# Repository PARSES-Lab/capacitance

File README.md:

# FDC1004 Capacitance Reading and Breakout Board Hardware 

This library provides basic functionality for the FDC1004 Capacitance to Digital Sensor. According to the datasheet, the FDC1004 provides femto-farad precision for measuring capacitances up to 115 pF in increments of 500 aF. The .ino files in examples demonstrate reading continuous values, triggered single values for multiple channels, and differential measurements. 

The breakout board provides shielded capacitance readings on four channels via a JST PH connector (v4). The board schematic and PCB files are included in the BreakoutBoard directory in this repository. Please see the Hardware file for more information about the breakout board design.

If you use this board in an academic project, please cite our work!

I. A. Mensah, D. Leblebicioglu and K. L. Dorsey, "Wireless Capacitive Measurement Board for Wearable or Proprioceptive Applications," 2025 IEEE 8th International Conference on Soft Robotics (RoboSoft), Lausanne, Switzerland, 2025, pp. 1-6, doi: 10.1109/RoboSoft63089.2025.11020828.

D. Leblebicioglu, I. A. Mensah, J. Allen, A. Vadivel, N. Hanson and K. L. Dorsey, "Capacitive Sensor Design for Soft Robots and Smart Garments," 2025 23rd International Conference on Solid-State Sensors, Actuators and Microsystems (Transducers), Orlando, FL, USA, 2025, pp. 414-418, doi: 10.1109/Transducers61432.2025.11110662.

## Hardware

 * A 3.3 V microcontroller board. The FDC1004 is incompatible with 5 V microcontrollers without additional care for the I2C bus voltage!
 * TI FDC1004: https://www.ti.com/product/FDC1004
 * 2 1.8k Ohm resistors to pull up SDA and SCL pins on I2C line (some microcontroller breakout boards may already have these on board)
 * A few non-polarized (e.g., ceramic) capacitors for test, in the range of 5 pF to 100 pF
 
## Limitations
 * This code has only been tested on the ESP32, ESP32-S2, and ESP32-S3 microcontroller breakout boards from Adafruit. It may not work on other 3.3 V microcontrollers such as the Adafruit Nano or Sparkfun Redboards that have 3.3 V logic levels. 
 * There is a potential bug when the FDC1004 is reading single (not repeated) measurements where it will read incorrectly. If you are getting unexpected behavior from the single read example, or no reading, push the continuous example first and then the single read example.

## Single-ended capacitance (channel to ground) or differential (channel to channel) readings: 
 * If first pin and second pin in configureMeasurement and triggerMeasurement functions are the same, it assumes a sigle-ended measurement
 * Otherwise, it assumes a differential measurement between those pins.
 * The convenience functions in the .cpp file (written by Beshaya) set the measurement type (single or continuous, which channels, measurement number/register)
 * Capacitors must always be placed from channel to ground. In differential measurements, they are still read by the difference between capacitance channels to ground. 

 ## Documentation on example functions
 
### float absoluteCapacitance(uint8_t measSlot, uint8_t chanA, uint8_t chanB, uint8_t measType, uint8_t * capdacPtr)
 * Calculates the absolute capaciance capacitanceAbsolute (relative + capdac) read off the FDC1004

 #### Parameters: 
 * measSlot : the measurement "slot" or number. This can be arbitrary between 0 and 3, or measA, measB... for convenience
 * chanA : the first pin you wish to measure capacitance to ground. Use pin definitions above for convenience.
 * chanB : the second pin you wish to measure capacitance to ground. Due to limitations of the FDC1004, chanB must be the same or greater value to chanA. Setting to the same value as chanA will set up a single-ended measurement. Setting at a higher value will set up a differential measurement. 
 * measType : Single (0) or repeated (1). Use measSingl and measCont for convenience. 
 * capdacPtr : A pointer to the global capdac value for that measurement. Labeled capdacA, capdacB... for convenience

 #### returns capacitanceAbsolute

* Notes: Calls configTrigRead in the case of a single measurement. Calls relativeCapacitance value in the case of a repeated measurement. If the returned capacitanceRelative reading is out of the +/- 15 pF limits for the FDC1004, it will call setCAPDAC. It converts capdac to a capacitance value in pF and adds to relative capacitance to find capacitanceAbsolute. If setCAPDAC was called, it will set the value of to capacitanceAbsolute -1

### float relativeCapacitance(uint8_t measSlot)
  * Reads the relative capacitance capacitanceRelative

#### Parameters: 
  * measSlot : the measurement "slot" or number. This can be arbitrary between 0 and 3, or measA, measB... for convenience

#### returns capacitanceRelative

* Notes: calls fdc.readMeasurement to read a 32-bit value (24-bit capacitance with 8 trailing zeroes, as per FDC1004 documentation) and convert into a capacitance reading with the ratio 15 pF/ 32676. The 16 most significant bits (MSB) are the only ones needed for the capacitance reading, since the measurement resolution is 0.5 fF and the max range is 30 pF. A 16 bit value in two's complement ranges from -32768 to 32767 (2^15 - 1) (i.e., resolution of ~0.46 fF with +/- 15 pF range). Therefore, we don't need to calculate the capacitance using the LSB since the most significant bit of LSB is below the measurement resolution/noise floor. We do still need to read LSB since the FDC1004 is expecting it to be read before the next measurement. The convenience functions in the .cpp file take care of this read.

### uint8_t setCAPDAC(uint8_t measSlot, uint8_t chanA, uint8_t chanB, uint8_t measType, uint8_t * capdacPtr)
* Resets capdac value. Will only execute if the measurement is single-ended (chanA and chanB are the same), because capdac cannot be set for a differential measurement.

#### Parameters:  
* measSlot : the measurement "slot" or number. This can be arbitrary between 0 and 3, or measA, measB... for convenience
* chanA : the first pin you wish to measure capacitance to ground. Use pin definitions above for convenience.
* chanB : the second pin you wish to measure capacitance to ground. Due to limitations of the FDC1004, chanB must be the same or greater value to chanA. Setting to the same value as chanA will set up a single-ended measurement. Setting at a higher value will set up a differential measurement. 
* measType : Single (0) or repeated (1). Use measSingl and measCont for convenience. 
* capdacPtr : the pointer to the global capdac associated with the measurement in measSlot

#### returns *capdacPtr (the dereference to the pointer to the global capdac associated with that measurement)

* Notes: Resets capdac to 0 and calls configTrigRead to read the relative value. While the new capdac value has not been found, it calls adjustCAPDAC, then calls configTrigRead in a loop until the timeout value (set to 30 by default). If a new capdac value is not found, it defaults to 0.

### uint8_t adjustCAPDAC(float capacitanceRelative, uint8_t * capdacPtr)
* Adjusts or increments capdac value and returns a flag stating whether it successfully reset.
 
#### Parameters: 
* capacitanceRelative : the relative capacitance reading fom the FDC
* capdacPtr : the pointer to the global capdac associated with the measurement in measSlot

#### returns capdacFlag, which says whether or not the capdac has been successfully reset.

* Notes: If the capdac is in range, it will try to find the capdac value that brings capacitanceRelative as close to 0 as possible to give the largest potential range, then return 0 to signal that capdac has been reset successfully. If capdac is not in range, it will incremenet or decrement capdac by 5 (15.625 pF) to bring it to the next range, then return 1 to signal that capdac needs to be set again.

### float configTrigRead(uint8_t measSlot, uint8_t chanA, uint8_t chanB, uint8_t measType, uint8_t capdac)
 * Configures and triggers the measurement and reads relative capacitance

 #### Parameters: 
 * measSlot : the measurement "slot" or number. This can be arbitrary between 0 and 3, or measA, measB... for convenience
 * chanA : the first pin you wish to measure capacitance to ground. Use pin definitions above for convenience.
 * chanB : the second pin you wish to measure capacitance to ground. Due to limitations of the FDC1004, chanB must be the same or greater value to chanA. Setting to the same value as chanA will set up a single-ended measurement. Setting at a higher value will set up a differential measurement. 
 * measType : Single (0) or repeated (1). Use measSingl and measCont for convenience. 
 * capdac : the global capdac value associated with that measurement.

 #### returns capacitanceRelative

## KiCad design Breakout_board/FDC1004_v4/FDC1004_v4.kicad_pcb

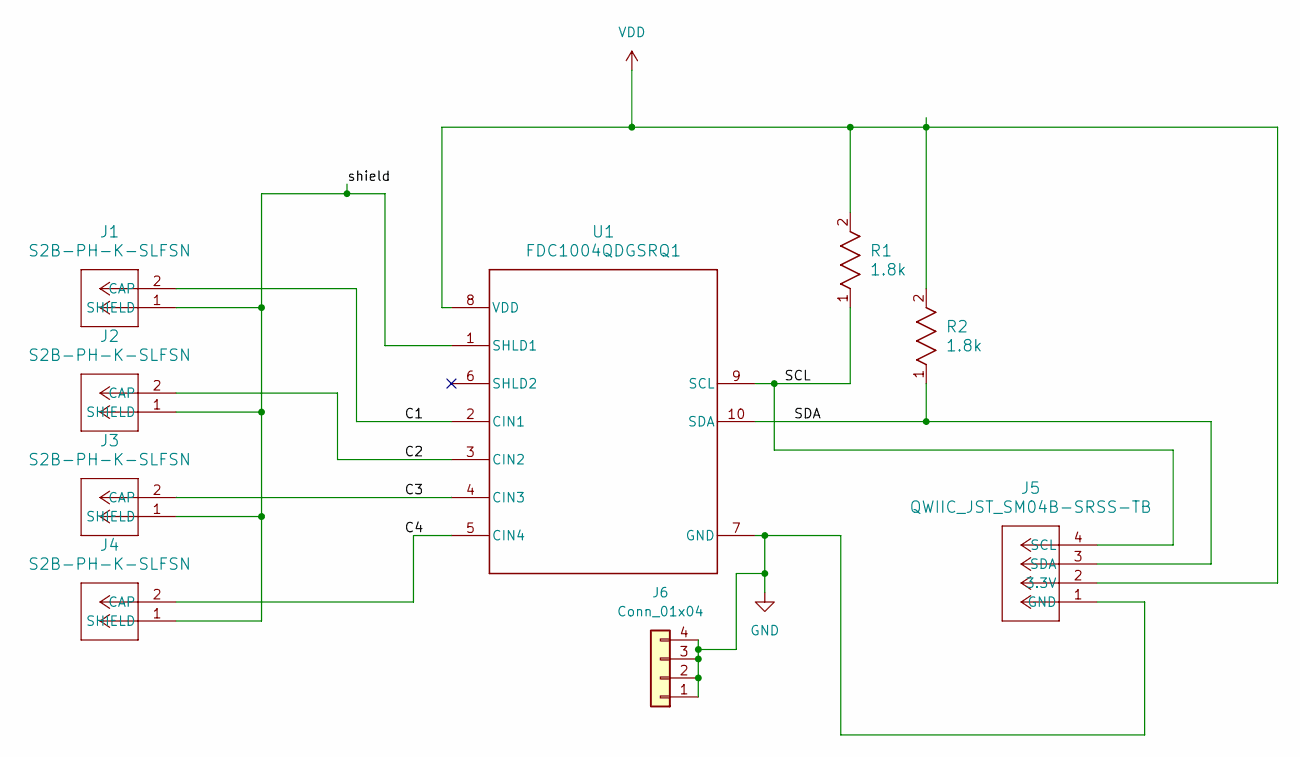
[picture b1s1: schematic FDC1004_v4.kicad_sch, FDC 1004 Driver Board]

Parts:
J1, J2, J3, J4: S2B-PH-K-SLFSN; CONN_S2B-PH-K-S_JST
J5: QWIIC_JST_SM04B-SRSS-TB; CONN_SM04B-SRSS-TB_JST_QWIIC
J6: Conn_01x04; PinHeader_1x04_P2.54mm_Vertical
R1, R2: 1.8k; R_1206_3216Metric_Pad1.30x1.75mm_HandSolder
U1: FDC1004QDGSRQ1; FDC1004DGS0010A_M

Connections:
/C1: J1.2 (CAP), U1.2 (CIN1)
/C2: J2.2 (CAP), U1.3 (CIN2)
/C3: J3.2 (CAP), U1.4 (CIN3)
/SCL: J5.4 (SCL), R1.1, U1.9 (SCL)
/SDA: J5.3 (SDA), R2.1, U1.10 (SDA)
/shield: J1.1 (SHIELD), J2.1 (SHIELD), J3.1 (SHIELD), J4.1 (SHIELD), U1.1 (SHLD1)
GND: J5.1 (GND), J6.1, J6.2, J6.3, J6.4, U1.7 (GND)
unnamed: J4.2 (CAP), U1.5 (CIN4)
VDD: J5.2 (3.3V), R1.2, R2.2, U1.8 (VDD)

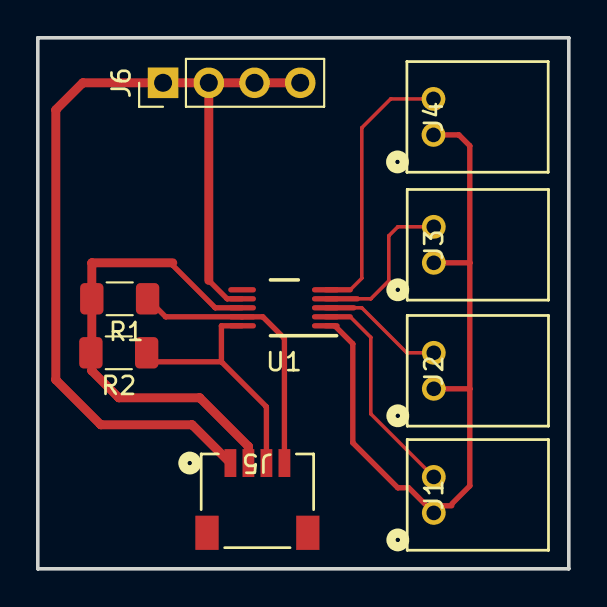
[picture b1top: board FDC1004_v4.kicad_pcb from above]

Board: 2 copper layers, 29.5 x 29.5 mm, 9 parts (0 on the bottom side), 9 nets.

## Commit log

2025-02-04 add missing semicolon
2025-03-10 update sampling rate in multichannel_read
2025-03-10 move functions to FDC1004 library
2025-04-09 Added capacitance arduino code and steps for logging capacitance and optitrack data
2025-04-14 serial communication ros2 topic echo is updated
2025-04-14 this is the serial communication code.
2025-04-14 Update steps for immanuel
2025-07-17 Update and rename miniFrank.py to ros_cap_publisher.py
    rename
2025-07-17 update library
2026-02-10 Add v4 board with FDC1004 breakout only
    QWIIC connector to any microcontroller and JST PH connectors instead of U.FL, which were not reliable
